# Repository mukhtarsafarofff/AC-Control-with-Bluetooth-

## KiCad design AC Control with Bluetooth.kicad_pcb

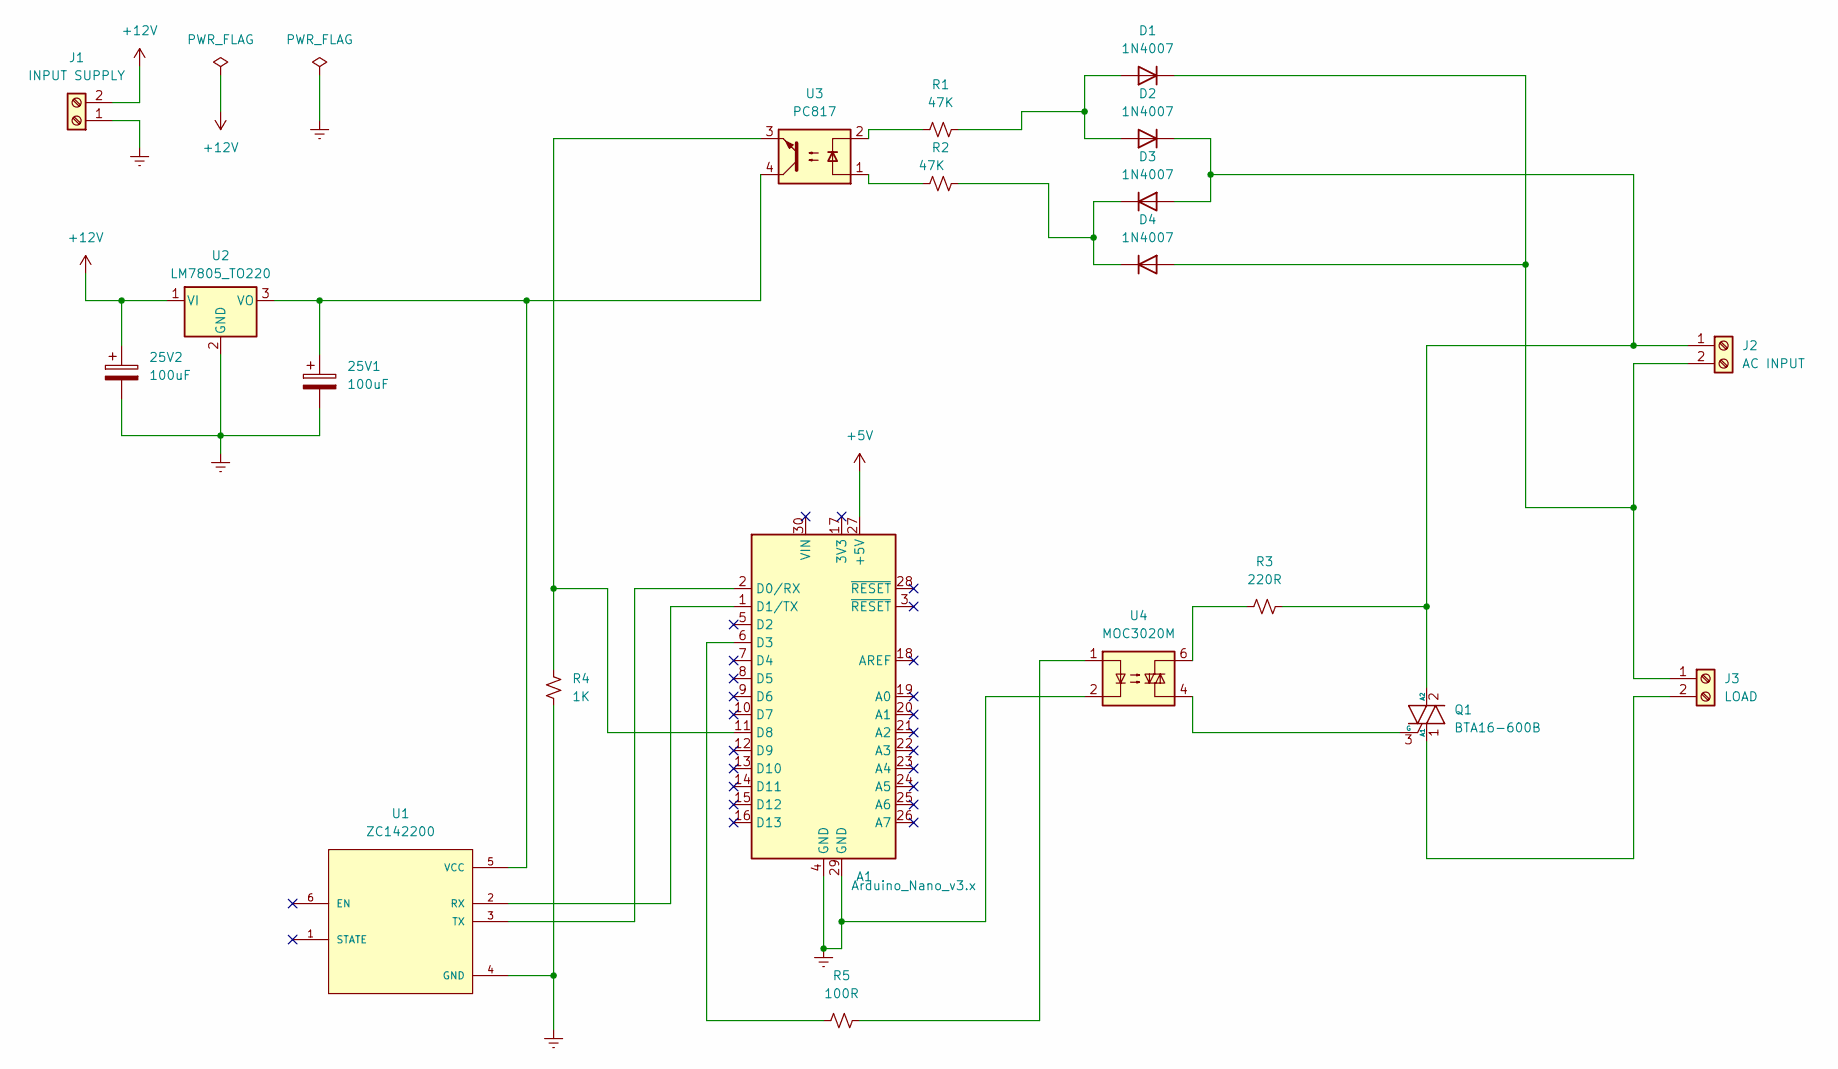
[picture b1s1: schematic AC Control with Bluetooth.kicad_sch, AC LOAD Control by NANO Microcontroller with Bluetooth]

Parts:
25V1, 25V2: 100uF; CP_Radial_D10.0mm_P7.50mm
A1: Arduino_Nano_v3.x; Arduino_Nano
D1, D2, D3, D4: 1N4007; D_DO-41_SOD81_P10.16mm_Horizontal
J1: INPUT SUPPLY; TerminalBlock_bornier-2_P5.08mm
J2: AC INPUT; TerminalBlock_bornier-2_P5.08mm
J3: LOAD; TerminalBlock_bornier-2_P5.08mm
Q1: BTA16-600B; TO-220-3_Vertical
R1, R2: 47K; R_Axial_DIN0411_L9.9mm_D3.6mm_P15.24mm_Horizontal
R3: 220R; R_Axial_DIN0411_L9.9mm_D3.6mm_P15.24mm_Horizontal
R4: 1K; R_Axial_DIN0411_L9.9mm_D3.6mm_P15.24mm_Horizontal
R5: 100R; R_Axial_DIN0411_L9.9mm_D3.6mm_P15.24mm_Horizontal
U1: ZC142200; MODULE_ZC142200; PARTREV N/A
U2: LM7805_TO220; TO-220-3_Vertical
U3: PC817; DIP-4_W7.62mm
U4: MOC3020M; DIP762W45P254L889H508Q6

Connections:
+5V: A1.27 (+5V)
+12V: 25V2.1, J1.2, U2.1 (VI)
Earth: 25V1.2, 25V2.2, A1.4 (GND), A1.29 (GND), J1.1, R4.1, U1.4 (GND), U2.2 (GND), U4.2
unnamed: A1.2 (D0/RX), U1.3 (TX)
unnamed: A1.1 (D1/TX), U1.2 (RX)
unnamed: A1.6 (D3), R5.2
unnamed: A1.11 (D8), R4.2, U3.3
unnamed: D1.2 (A), D2.2 (A), R1.2
unnamed: D1.1 (K), D4.2 (A), J2.2, J3.1
unnamed: D2.1 (K), D3.2 (A), J2.1, Q1.2 (A2), R3.2
unnamed: D3.1 (K), D4.1 (K), R2.2
unnamed: J3.2, Q1.1 (A1)
unnamed: Q1.3 (G), U4.4
unnamed: R1.1, U3.2
unnamed: R2.1, U3.1
unnamed: R3.1, U4.6
unnamed: R5.1, U4.1
unnamed: 25V1.1, U1.5 (VCC), U2.3 (VO), U3.4

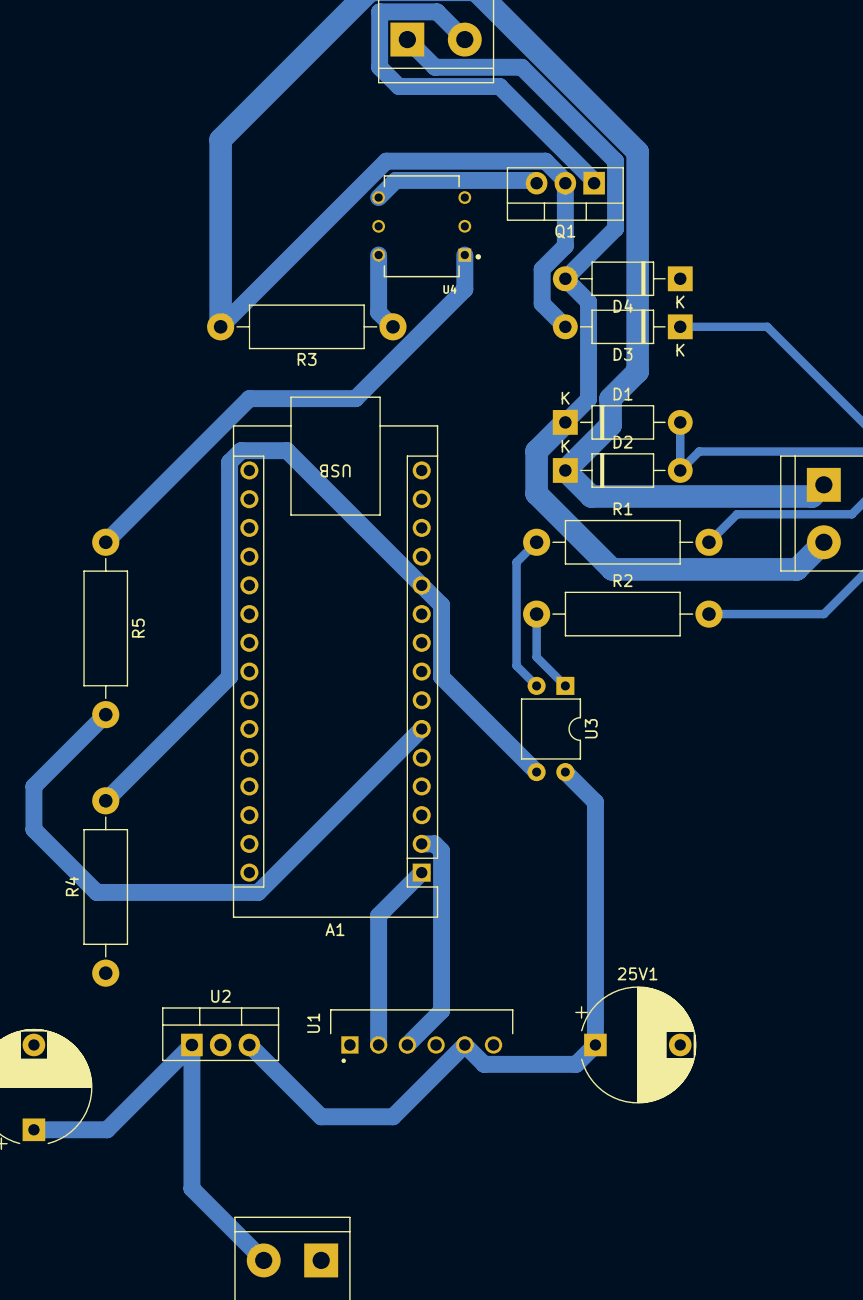
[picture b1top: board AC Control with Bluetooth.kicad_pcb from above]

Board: 2 copper layers, 20 parts (0 on the bottom side), 17 nets.

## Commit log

2024-03-23 Ac control with Bluetooth is accomplished
2024-03-23 AC Control with Bluetooth is restored
